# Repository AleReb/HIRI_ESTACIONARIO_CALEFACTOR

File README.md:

# HIRI AUCA con calefactor para Plantower

Proyecto de firmware y hardware para una estación ambiental HIRI AUCA basada en
ESP32, un sensor Plantower y un calefactor controlado por ESP8266. El calefactor
mide temperatura y humedad, protege el elemento térmico mediante termocupla y
entrega sus datos a la estación por un enlace serial dedicado.

## Estado vigente

| Componente | Archivo principal | Plataforma | Versión |
|---|---|---|---|
| Calefactor | `Calefactor_V2_0_0/Calefactor_V2_0_0.ino` | ESP8266 / NodeMCU | Firmware `1.0.0` |
| Estación HIRI | `HIRI_STATIC_CALEFACTOR_0_1/HIRI_STATIC_CALEFACTOR_0_1.ino` | ESP32 Dev Module | `CAL V0.0.1` |
| PCB calefactor | `PCB/calefactor.sch` y `PCB/calefactor.brd` | Autodesk EAGLE 9.6.2 | Diseño fuente |
| PCB HIRI ESP32/SIM7600 | `PCB/pcbesp32sim7600/Board_760032v2.sch` y `PCB/pcbesp32sim7600/Board_760032v2.brd` | Autodesk EAGLE 9.6.2 | Diseño fuente |
| PCB resistivo | `PCB/RESIS-CALOR.brd` | Autodesk EAGLE 9.6.2 | Diseño fuente |

El firmware histórico con DHT22 se conserva sólo como referencia. El calefactor
vigente usa SHT40; no requiere DHT22.

## Funciones principales

### Calefactor

- SHT40 para temperatura y humedad.
- BME280 como medición interna/respaldo.
- MAX6675 y termocupla para protección térmica.
- Relé en `D0`.
- Control por humedad con histéresis: enciende desde `65 % RH` y libera bajo
  `60 % RH`.
- Control por temperatura ambiental baja.
- Corte a `70 °C` y emergencia a `80 °C`.
- Prueba remota temporizada de 1 a 300 segundos, siempre subordinada a la
  protección térmica.
- Reinicio programado cada 4 horas.

### HIRI AUCA

- Plantower PMS por software serial.
- Enlace independiente a 9600 baudios con el calefactor.
- OLED SSD1306, RTC DS3231, tarjeta SD, batería y NeoPixel.
- SIM7600 para red celular, HTTP y GNSS configurable.
- Guardado SD cada 3 minutos y envío HTTP cada 5 minutos.
- Consulta opcional de versión del calefactor, sin bloquear calefactores
  antiguos.

## Protocolo serial HIRI-calefactor

Las tramas son ASCII a `9600 8N1` y terminan en `*HH`, donde `HH` es la suma
de comprobación hexadecimal de 8 bits del texto anterior al asterisco.

El identificador vigente del calefactor es `CALEF`; HIRI también acepta `CAL`
para equipos anteriores.

```text
HIRI,1,HELLO*HH
CALEF,1,HELLO,1.0.0*HH

HIRI,1,VERSION*HH
CALEF,1,VERSION,1.0.0*HH

HIRI,1,TEMP,valor*HH
HIRI,1,CAL,segundos*HH

CALEF,1,DATA,tempExt,tempSHT,tempBME,humSHT,humBME,tempTermocupla,
             rele,porHumedad,porTemperatura,emergencia*HH
```

La consulta `VERSION` es opcional. HIRI la envía al arrancar y luego cada 30
segundos durante un máximo de 3 minutos. La ausencia de respuesta no detiene el
arranque, la adquisición, el guardado ni el uso del calefactor.

## Estructura

- `Calefactor_V2_0_0/`: firmware vigente del calefactor.
- `HIRI_STATIC_CALEFACTOR_0_1/`: firmware vigente de la estación.
- `PCB/`: esquemáticos y placas EAGLE del calefactor, del elemento resistivo y
  de la estación HIRI con ESP32/SIM7600; consultar su README antes de fabricar.
- `documentacion/`: documentación del calefactor, cambios y antecedentes.
- `codigo_original/`: respaldos históricos; no son el firmware recomendado.

## Compilación

```powershell
arduino-cli compile --fqbn esp8266:esp8266:nodemcuv2 Calefactor_V2_0_0
arduino-cli compile --fqbn esp32:esp32:esp32 HIRI_STATIC_CALEFACTOR_0_1
```

Se requieren las librerías Arduino indicadas por los `#include` de cada
sketch. Antes de cargar, sustituir el puerto de ejemplo por el puerto real.

## Documentación

- [Documentación del calefactor](documentacion/README.md)
- [Documentación de HIRI](HIRI_STATIC_CALEFACTOR_0_1/README.md)
- [PCB y advertencias de fabricación](PCB/README.md)
- [Licencia y atribución](LICENSE.md)
- [Descargo de responsabilidad](DISCLAIMER.md)

## Autor y licencia

Creación original: **Alejandro Rebolledo**

Contacto: **arebolledo@udd.cl**

Salvo los componentes de terceros identificados por separado, el firmware, la
documentación y los diseños PCB originales de este repositorio se ofrecen bajo
[Creative Commons Attribution-NonCommercial 4.0 International](LICENSE.md).
Se permite compartir y adaptar con atribución, únicamente para fines no
comerciales. El uso comercial requiere autorización separada del autor.

Este proyecto se entrega tal cual y no constituye un producto certificado.
Revise el [descargo de responsabilidad](DISCLAIMER.md) antes de construir,
energizar o desplegar el equipo.

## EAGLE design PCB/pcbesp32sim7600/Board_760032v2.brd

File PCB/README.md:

# Diseños PCB

Esta carpeta contiene fuentes de Autodesk EAGLE 9.6.2:

| Archivo | Contenido observado | Dimensión aproximada |
|---|---|---:|
| `calefactor.sch` | Esquemático del controlador del calefactor, 1 hoja y 11 componentes | No aplica |
| `calefactor.brd` | Placa del controlador con Wemos D1 Mini Pro, termocupla, dos conectores I2C, relé y serial | 48,30 × 78,09 mm |
| `RESIS-CALOR.brd` | Placa alargada del elemento resistivo/calefactor | 120,40 × 24,00 mm |
| `pcbesp32sim7600/Board_760032v2.sch` | Esquemático de la estación HIRI para ESP32 y SIM7600 | No aplica |
| `pcbesp32sim7600/Board_760032v2.brd` | Placa de la estación HIRI correspondiente al firmware `HIRI_STATIC_CALEFACTOR_0_1` | Fuente EAGLE |

## Correspondencia con el firmware

El firmware vigente usa:

- Wemos/ESP8266;
- MAX6675 y termocupla;
- BME280 y SHT40 por I2C;
- relé;
- enlace serial con HIRI.

El esquemático y la placa conservan un conector rotulado `DHT`. Es una herencia
del diseño anterior y no significa que el firmware vigente utilice DHT22. El
SHT40 vigente se conecta por I2C. Antes de fabricar se debe comprobar en EAGLE
la asignación real de cada conector, señal y pin contra
`Calefactor_V2_0_0/Calefactor_V2_0_0.ino`.

El diseño `pcbesp32sim7600/Board_760032v2` corresponde al firmware de la
estación ubicado en
`HIRI_STATIC_CALEFACTOR_0_1/HIRI_STATIC_CALEFACTOR_0_1.ino`. Incluye la placa y
el esquemático para la electrónica basada en ESP32 y SIM7600, además de las
conexiones de los periféricos de HIRI. Antes de fabricar, también se deben
comparar las señales y los pines del diseño contra ese sketch.

## Estado de fabricación

No se incluyen Gerbers, archivos de perforado, BOM aprobada ni resultados de
DRC/ERC. Estos archivos deben considerarse fuentes editables, no un paquete de
fabricación liberado.

Antes de fabricar:

1. Ejecutar ERC en `calefactor.sch`.
2. Confirmar que `calefactor.brd` corresponde al esquemático vigente.
3. Ejecutar DRC con las reglas del fabricante.
4. Revisar anchos de pista, corriente, separación y aislamiento del circuito
   térmico y del relé.
5. Verificar huellas, polaridades, conectores y dimensiones mecánicas.
6. Revisar `RESIS-CALOR.brd` mediante cálculo térmico y eléctrico independiente.
7. Generar y revisar Gerbers y perforaciones antes de enviar a producción.
8. Ejecutar ERC y DRC sobre `pcbesp32sim7600/Board_760032v2.sch` y
   `pcbesp32sim7600/Board_760032v2.brd`, y verificar su correspondencia con el
   firmware HIRI vigente.

Consulte [el descargo de responsabilidad](../DISCLAIMER.md). Los diseños
originales se distribuyen bajo [CC BY-NC 4.0](../LICENSE.md).

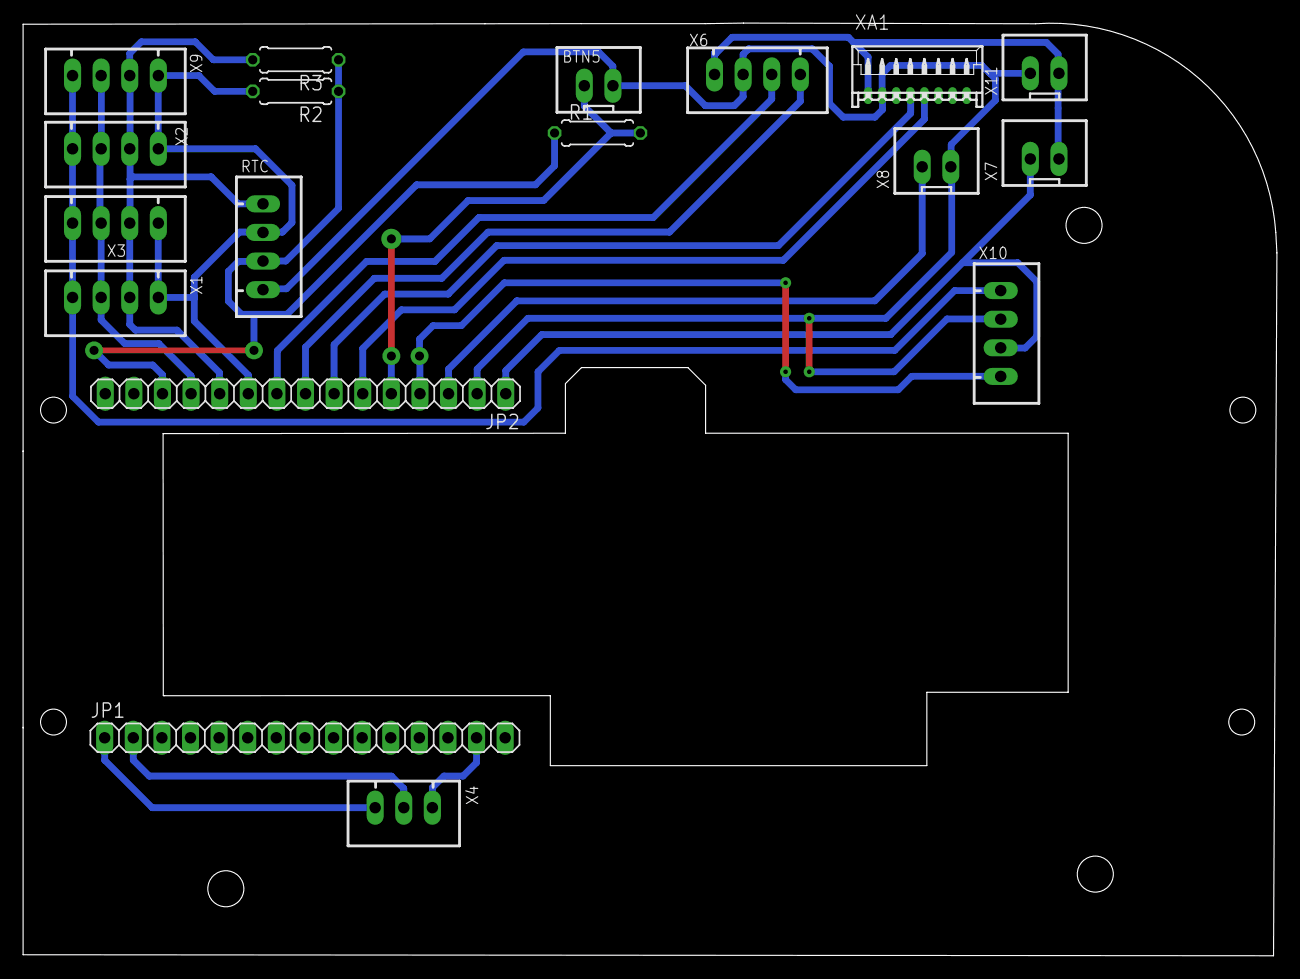
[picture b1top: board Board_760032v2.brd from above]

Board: 2 copper layers, 111.3 x 82.8 mm, 18 parts (0 on the bottom side), 16 nets.

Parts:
BTN5: JST-XH-02-PIN-LONG-PAD; JST-XH-02-PACKAGE-LONG-PAD
JP1, JP2: 1X15
R1, R2, R3: 0207/7
RTC: JST-XH-04-PIN-LONG-PAD; JST-XH-04-PACKAGE-LONG-PAD
X1, X2, X3, X6, X9, X10: JST-XH-04-PIN-LONG-PAD; JST-XH-04-PACKAGE-LONG-PAD
X4: JST-XH-03-PIN-LONG-PAD; JST-XH-03-PACKAGE-LONG-PAD
X7: btn0; JST-XH-02-PACKAGE-LONG-PAD
X8, X11: JST-XH-02-PIN-LONG-PAD; JST-XH-02-PACKAGE-LONG-PAD
XA1: 53048-0810; MOLEX_53048-0810

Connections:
0: JP2.4, X10.4
3V3: JP2.13, R1.2, R2.1, R3.1, RTC.3
3V3B: JP1.1, X4.3
BTN: BTN5.1, JP2.5, R1.1
GND: BTN5.2, JP2.2, JP2.12, RTC.4, X1.3, X2.3, X3.3, X6.3, X8.2, X9.3, X10.2, X11.1, XA1.7
GND2: JP1.2, X4.2
OUT: X1.4, X2.4, X3.4, X9.4, X10.1
RGB: JP1.14, X4.1
RST: JP2.3, X8.1
RX1: JP2.9, X6.2
RX2: JP2.7, XA1.5
SCL: JP2.11, R3.2, RTC.1, X1.2, X2.2, X3.2, X9.2
SDA: JP2.10, R2.2, RTC.2, X1.1, X2.1, X3.1, X9.1
TX1: JP2.8, X6.1
TX2: JP2.6, XA1.4
VBUS: JP2.1, X6.4, X7.1, X7.2, X10.3, X11.2, XA1.8

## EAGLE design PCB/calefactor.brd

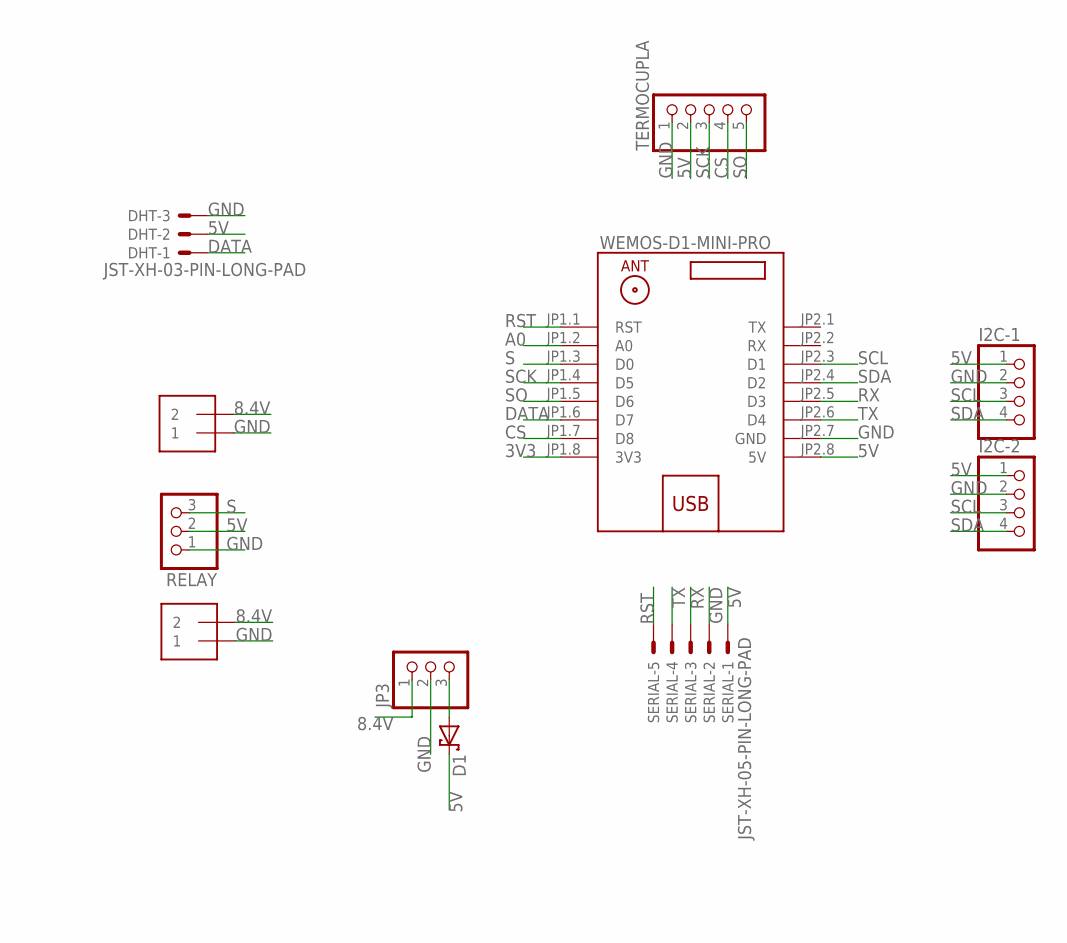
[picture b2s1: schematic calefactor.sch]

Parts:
D1: SCHOTTKY-DIODEDO41-7; DO41-7
DHT: JST-XH-03-PIN-LONG-PAD; JST-XH-03-PACKAGE-LONG-PAD
I2C-1, I2C-2: PINHD-1X4; 1X04
J1, J2: 1X2-3.5MM
JP3: PINHD-1X3; 1X03
RELAY: PINHD-1X3; 1X03
SERIAL: JST-XH-05-PIN-LONG-PAD; JST-XH-05-PACKAGE-LONG-PAD
TERMOCUPLA: PINHD-1X5; 1X05
U$1: WEMOS-D1-MINI-PRO

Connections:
3V3: U$1.JP1.8 (3V3)
5V: D1.C, DHT.2, I2C-1.1, I2C-2.1, RELAY.2, SERIAL.1, TERMOCUPLA.2, U$1.JP2.8 (5V)
8.4V: J1.2, J2.2, JP3.1
A0: U$1.JP1.2 (A0)
CS: TERMOCUPLA.4, U$1.JP1.7 (D8)
DATA: DHT.1, U$1.JP1.6 (D7)
GND: DHT.3, I2C-1.2, I2C-2.2, J1.1, J2.1, JP3.2, RELAY.1, SERIAL.2, TERMOCUPLA.1, U$1.JP2.7 (GND)
unnamed: D1.A, JP3.3
RST: SERIAL.5, U$1.JP1.1 (RST)
RX: SERIAL.3, U$1.JP2.5 (D3)
S: RELAY.3, U$1.JP1.3 (D0)
SCK: TERMOCUPLA.3, U$1.JP1.4 (D5)
SCL: I2C-1.3, I2C-2.3, U$1.JP2.3 (D1)
SDA: I2C-1.4, I2C-2.4, U$1.JP2.4 (D2)
SO: TERMOCUPLA.5, U$1.JP1.5 (D6)
TX: SERIAL.4, U$1.JP2.6 (D4)

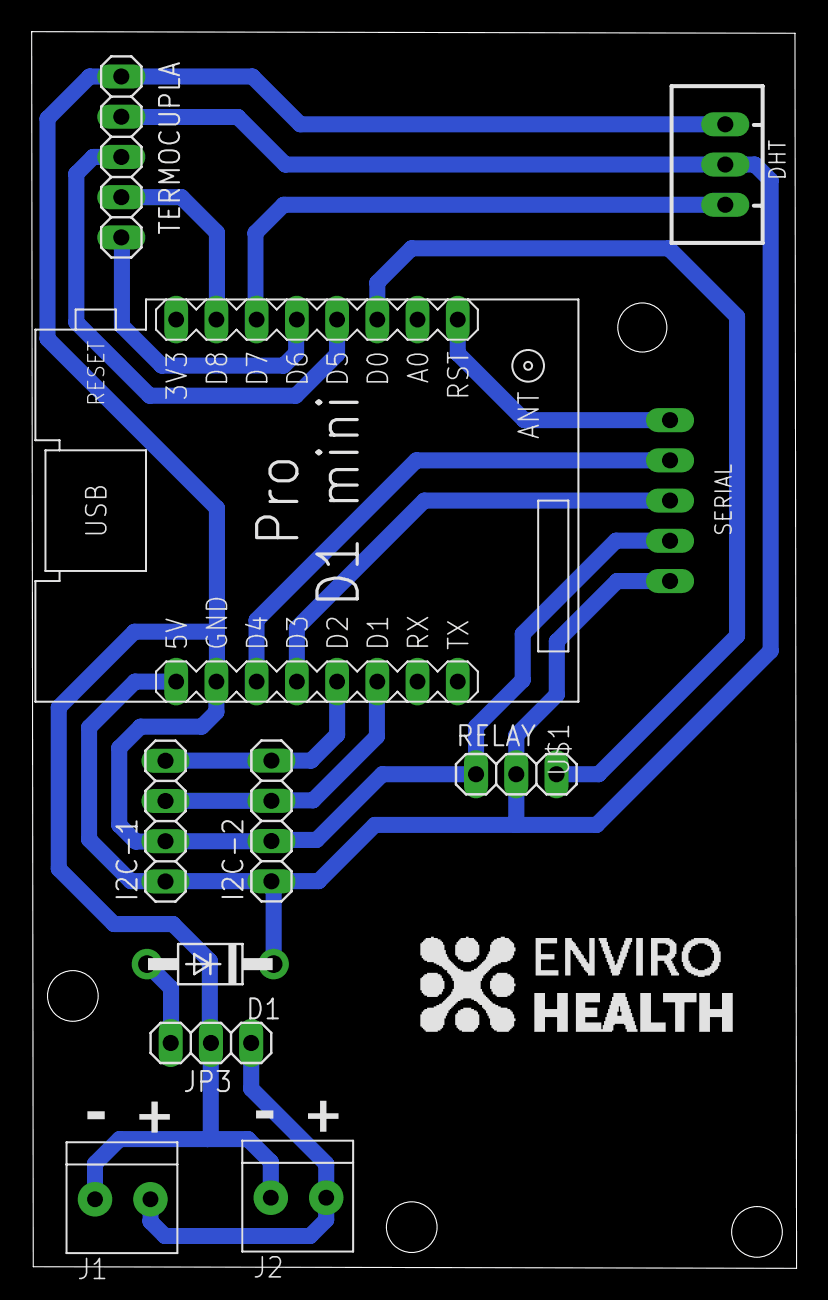
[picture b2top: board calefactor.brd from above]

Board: 2 copper layers, 48.3 x 78.1 mm, 11 parts (0 on the bottom side), 14 nets.

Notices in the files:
parts and their libraries:
diy-modules: Released under the Creative Commons Attribution 4.0 International License: http://creativecommons.org/licenses/by/4.0
